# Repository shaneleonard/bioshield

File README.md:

# bioshield
Arduino shield for biomedical instrumentation. Includes an ECG, ICG, and PPG. For educational purposes.

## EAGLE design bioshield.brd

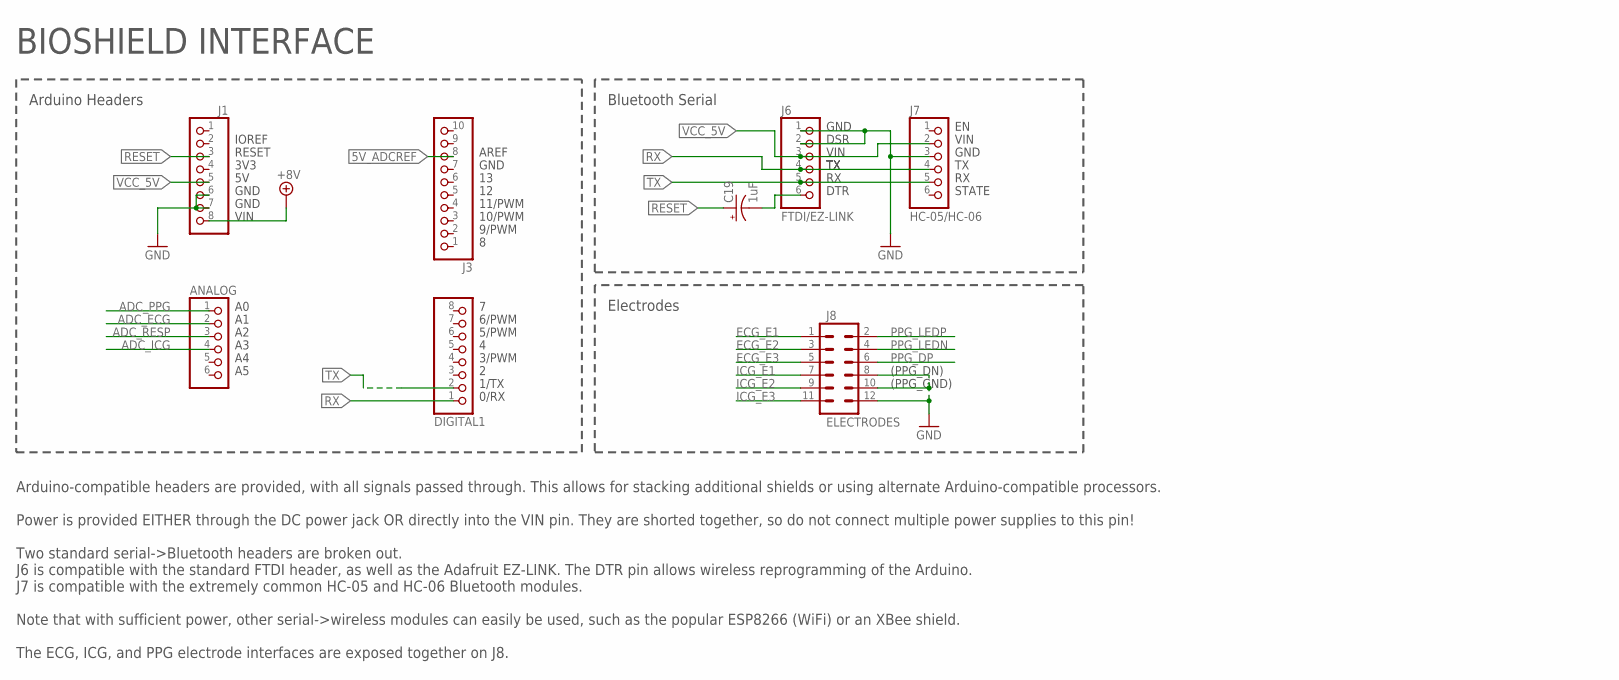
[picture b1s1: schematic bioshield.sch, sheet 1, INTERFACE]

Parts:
ANALOG: PINHD-1X6; 1X06
C19: 1uF; E2-5
DIGITAL1: PINHD-1X8TH; 1X08-TH
J1: PINHD-1X8TH; 1X08-TH
J3: PINHD-1X10TH; 1X10-TH
J6: FTDI/EZ-LINK; 1X06
J7: HC-05/HC-06; 1X06
J8: ELECTRODES; 2X6

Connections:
5V_ADCREF: J3.8; also elsewhere on the board
+8V: J1.8; also elsewhere on the board
ADC_ECG: ANALOG.2; also elsewhere on the board
ADC_ICG: ANALOG.4; also elsewhere on the board
ADC_PPG: ANALOG.1; also elsewhere on the board
ADC_RESP: ANALOG.3; also elsewhere on the board
ECG_E1: J8.1; also elsewhere on the board
ECG_E2: J8.3; also elsewhere on the board
ECG_E3: J8.5; also elsewhere on the board
GND: J1.6, J1.7, J6.1, J6.2, J7.3, J8.8, J8.10, J8.12; also elsewhere on the board
ICG_E1: J8.7; also elsewhere on the board
ICG_E2: J8.9; also elsewhere on the board
ICG_E3: J8.11; also elsewhere on the board
unnamed: C19.-, J6.6
PPG_DP: J8.6; also elsewhere on the board
PPG_LEDN: J8.4; also elsewhere on the board
PPG_LEDP: J8.2; also elsewhere on the board
RESET: C19.+, J1.3
RX: DIGITAL1.1, J6.4, J7.4
TX: DIGITAL1.2, J6.5, J7.5
VCC_5V: J1.5, J6.3, J7.2; also elsewhere on the board

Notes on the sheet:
BIOSHIELD INTERFACE
IOREF
RESET
3V3
GND
VIN
AREF
11/PWM
10/PWM
9/PWM
6/PWM
5/PWM
3/PWM
1/TX
0/RX
DSR
DTR
STATE
Arduino Headers
Bluetooth Serial
Electrodes
Arduino-compatible headers are provided, with all signals passed through. This allows for stacking additional shields or using alternate Arduino-compatible processors. Power is provided EITHER through the DC power jack OR directly into the VIN pin. They are shorted together, so do not connect multi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
(PPG_DN)
(PPG_GND)

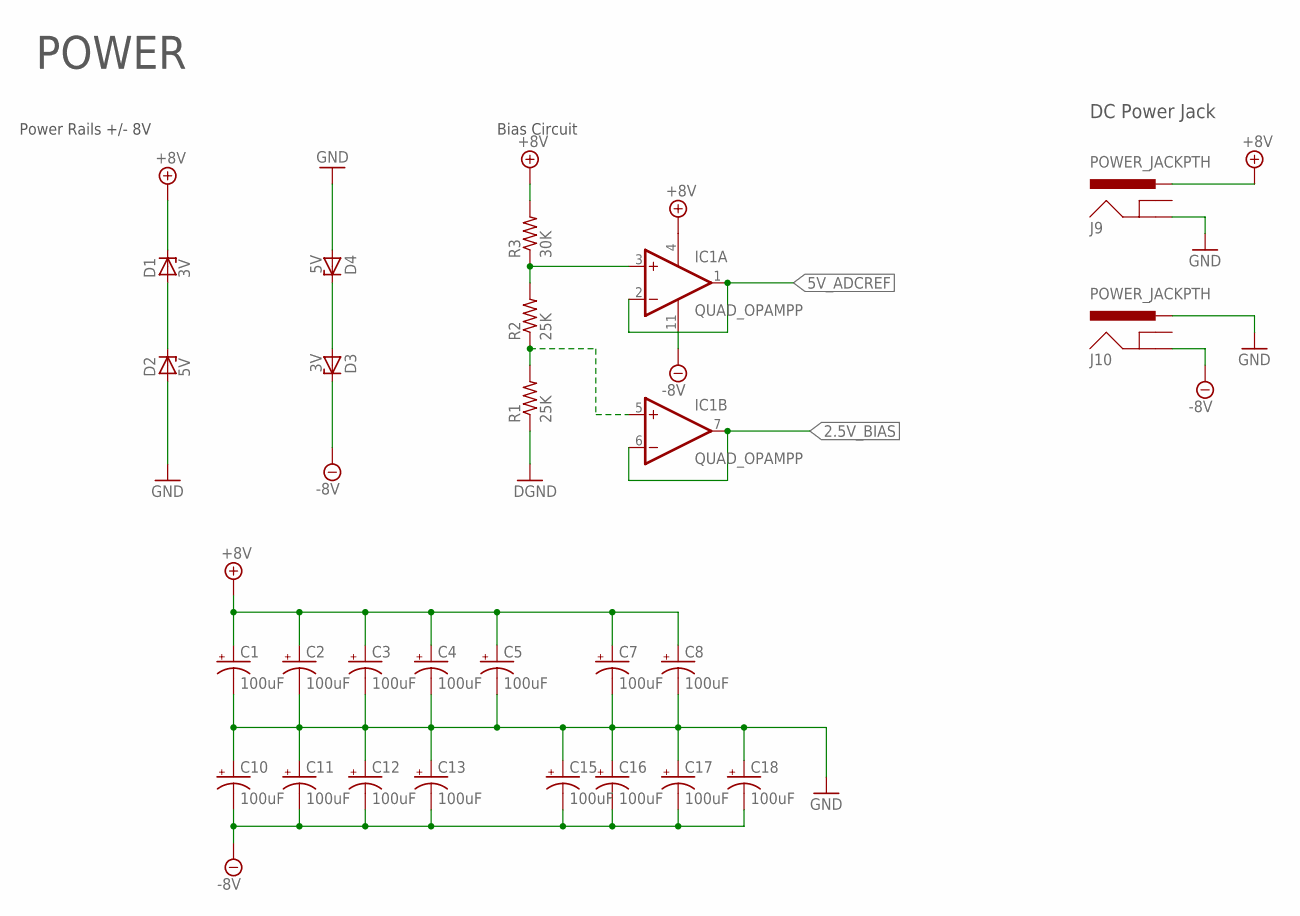
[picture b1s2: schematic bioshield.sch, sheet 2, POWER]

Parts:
C1, C2, C3, C4, C5, C7, C8, C10, C11, C12, C13, C15, C16, C17, C18: 100uF; CPOL-RADIAL-100UF-25V
D1, D3: 3V; ZDIO-10
D2, D4: 5V; ZDIO-10
IC1: QUAD_OPAMPP; DIL14
J9, J10: POWER_JACKPTH; POWER_JACK_PTH
R1, R2: 25K; 0207/10
R3: 30K; 0207/10

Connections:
2.5V_BIAS: IC1.6 (-IN), IC1.7 (OUT); also elsewhere on the board
5V_ADCREF: IC1.1 (OUT), IC1.2 (-IN); also elsewhere on the board
+8V: C1.1 (+), C2.1 (+), C3.1 (+), C4.1 (+), C5.1 (+), C7.1 (+), C8.1 (+), D1.C, IC1.4 (V+), J9.PWR, R3.2; also elsewhere on the board
-8V: C10.2 (-), C11.2 (-), C12.2 (-), C13.2 (-), C15.2 (-), C16.2 (-), C17.2 (-), C18.2 (-), D3.C, IC1.11 (V-), J10.GND; also elsewhere on the board
GND: C1.2 (-), C2.2 (-), C3.2 (-), C4.2 (-), C5.2 (-), C7.2 (-), C8.2 (-), C10.1 (+), C11.1 (+), C12.1 (+), C13.1 (+), C15.1 (+), C16.1 (+), C17.1 (+), C18.1 (+), D2.A, D4.A, J9.GND, J10.PWR, R1.1; also elsewhere on the board
unnamed: IC1.5 (+IN), R1.2, R2.1
unnamed: D1.A, D2.C
unnamed: IC1.3 (+IN), R2.2, R3.1
unnamed: D3.A, D4.C

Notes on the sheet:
POWER
Power Rails +/- 8V
Bias Circuit
DC Power Jack

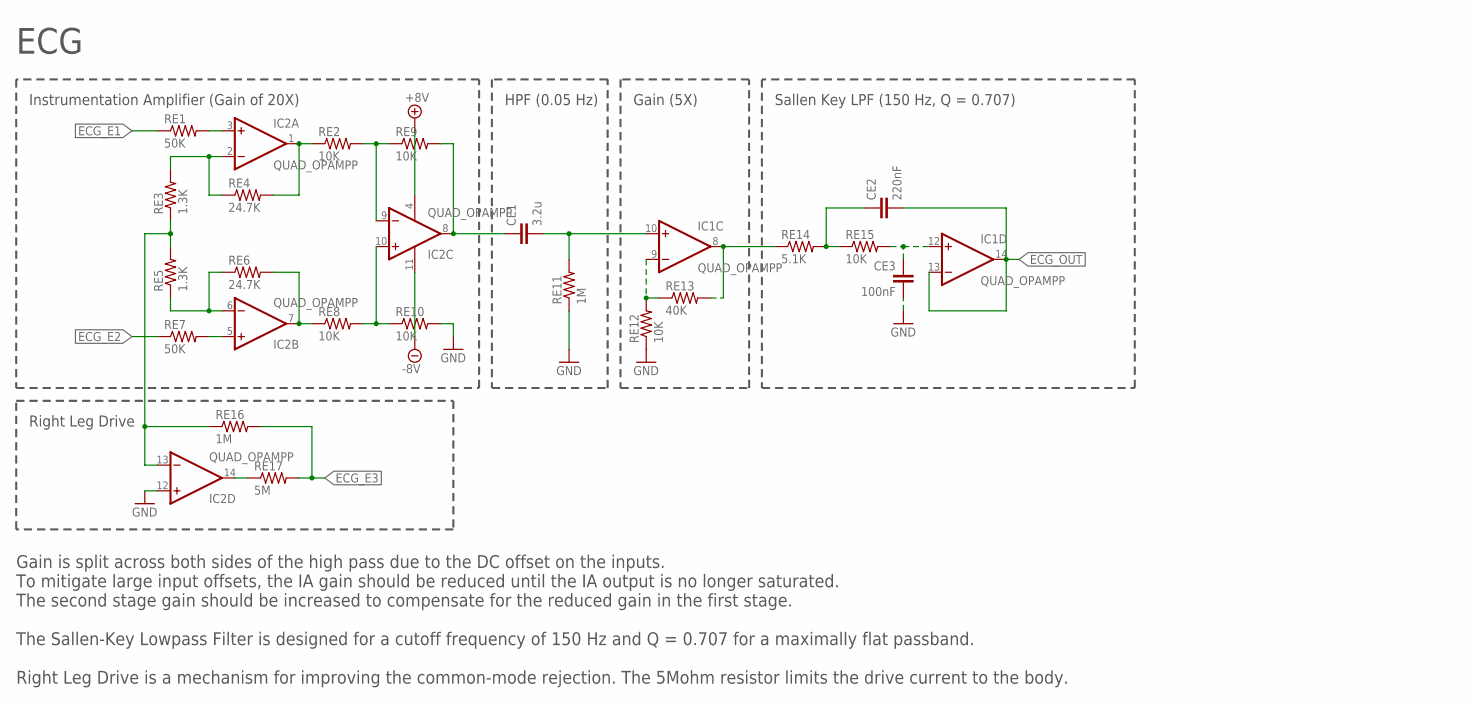
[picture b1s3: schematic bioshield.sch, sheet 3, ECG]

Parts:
CE1: 3.2u; CAP-PTH-5MM
CE2: 220nF; CAP-PTH-5MM
CE3: 100nF; CAP-PTH-5MM
IC1, IC2: QUAD_OPAMPP; DIL14
RE1, RE7: 50K; 0207/10
RE2, RE8, RE9, RE10, RE12, RE15: 10K; 0207/10
RE3, RE5: 1.3K; 0207/10
RE4, RE6: 24.7K; 0207/10
RE11, RE16: 1M; 0207/10
RE13: 40K; 0207/10
RE14: 5.1K; 0207/10
RE17: 5M; 0207/10

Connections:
+8V: IC2.4 (V+); also elsewhere on the board
-8V: IC2.11 (V-); also elsewhere on the board
ECG_E1: RE1.1; also elsewhere on the board
ECG_E2: RE7.1; also elsewhere on the board
ECG_E3: RE16.2, RE17.2; also elsewhere on the board
ECG_OUT: CE2.2, IC1.13 (-IN), IC1.14 (OUT); also elsewhere on the board
GND: CE3.2, IC2.12 (+IN), RE10.2, RE11.1, RE12.1; also elsewhere on the board
unnamed: IC1.9 (-IN), RE12.2, RE13.1
unnamed: CE1.2, IC1.10 (+IN), RE11.2
unnamed: CE3.1, IC1.12 (+IN), RE15.2
unnamed: IC1.8 (OUT), RE13.2, RE14.1
unnamed: CE2.1, RE14.2, RE15.1
unnamed: IC2.14 (OUT), RE17.1
unnamed: IC2.5 (+IN), RE7.2
unnamed: IC2.13 (-IN), RE3.1, RE5.2, RE16.1
unnamed: IC2.6 (-IN), RE5.1, RE6.1
unnamed: IC2.7 (OUT), RE6.2, RE8.1
unnamed: IC2.10 (+IN), RE8.2, RE10.1
unnamed: IC2.2 (-IN), RE3.2, RE4.1
unnamed: IC2.1 (OUT), RE2.1, RE4.2
unnamed: IC2.3 (+IN), RE1.2
unnamed: IC2.9 (-IN), RE2.2, RE9.1
unnamed: CE1.1, IC2.8 (OUT), RE9.2

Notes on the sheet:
Instrumentation Amplifier (Gain of 20X)
HPF (0.05 Hz)
Gain (5X)
Sallen Key LPF (150 Hz, Q = 0.707)
Right Leg Drive
ECG
Gain is split across both sides of the high pass due to the DC offset on the inputs. To mitigate large input offsets, the IA gain should be reduced until the IA output is no longer saturated. The second stage gain should be increased to compensate for the reduced gain in the first stage. The Sallen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

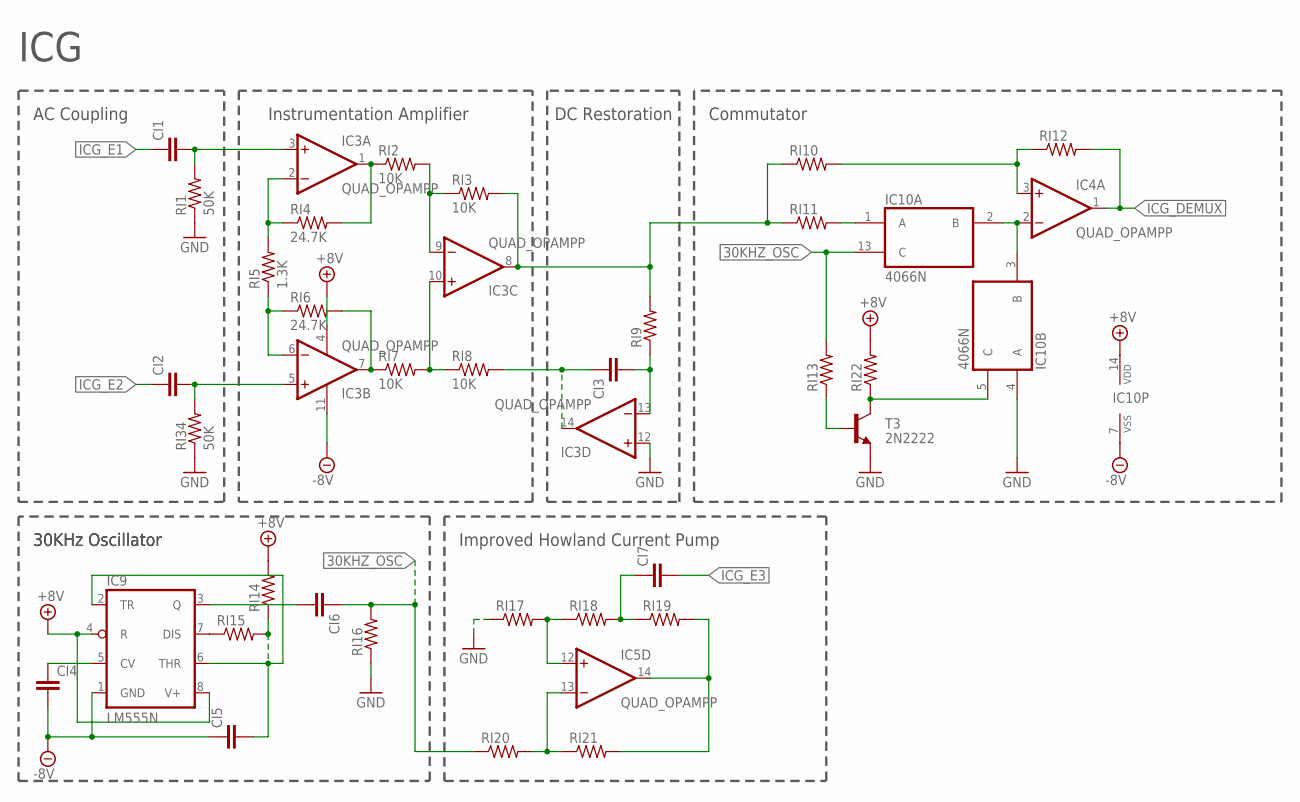
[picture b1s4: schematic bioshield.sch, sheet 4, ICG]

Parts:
CI1, CI2, CI3, CI4, CI5, CI6, CI7: CAPPTH1; CAP-PTH-5MM
IC3, IC4, IC5: QUAD_OPAMPP; DIL14
IC9: LM555N; DIL08
IC10: 4066N; DIL14
RI1, RI34: 50K; 0207/10
RI2, RI3, RI7, RI8: 10K; 0207/10
RI4, RI6: 24.7K; 0207/10
RI5: 1.3K; 0207/10
RI9, RI10, RI11, RI12, RI13, RI14, RI15, RI16, RI17, RI18, RI19, RI20, RI21, RI22: R-US_0207/10; 0207/10
T3: 2N2222; TO92-EBC-OVAL

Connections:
30KHZ_OSC: CI6.1, IC10.13 (C), RI13.2, RI16.2, RI20.1
+8V: IC3.4 (V+), IC9.4 (R), IC9.8 (V+), IC10.14 (VDD), RI14.2, RI22.2; also elsewhere on the board
-8V: CI4.2, CI5.1, IC3.11 (V-), IC9.1 (GND), IC10.7 (VSS); also elsewhere on the board
ELECTRODE3: CI7.1, RI18.2, RI19.1
GND: IC3.12 (+IN), IC10.4 (A), RI1.1, RI16.1, RI17.1, RI34.1, T3.E; also elsewhere on the board
ICG_DEMUX: IC4.1 (OUT), RI12.2; also elsewhere on the board
ICG_E1: CI1.1; also elsewhere on the board
ICG_E2: CI2.1; also elsewhere on the board
ICG_E3: CI7.2; also elsewhere on the board
unnamed: CI2.2, IC3.5 (+IN), RI34.2
unnamed: CI3.1, IC3.14 (OUT), RI8.2
unnamed: IC3.6 (-IN), RI5.1, RI6.1
unnamed: IC3.7 (OUT), RI6.2, RI7.1
unnamed: CI5.2, IC9.2 (TR), IC9.6 (THR), RI14.1, RI15.2
unnamed: IC10.1 (A), RI11.2
unnamed: IC9.7 (DIS), RI15.1
unnamed: IC4.2 (-IN), IC10.2 (B), IC10.3 (B)
unnamed: RI13.1, T3.B
unnamed: CI4.1, IC9.5 (CV)
unnamed: CI6.2, IC9.3 (Q)
unnamed: IC3.10 (+IN), RI7.2, RI8.1
unnamed: IC3.2 (-IN), RI4.1, RI5.2
unnamed: IC3.1 (OUT), RI2.1, RI4.2
unnamed: CI1.2, IC3.3 (+IN), RI1.2
unnamed: IC3.9 (-IN), RI2.2, RI3.1
unnamed: IC3.8 (OUT), RI3.2, RI9.2, RI10.1, RI11.1
unnamed: IC5.13 (-IN), RI20.2, RI21.1
unnamed: IC5.12 (+IN), RI17.2, RI18.1
unnamed: CI3.2, IC3.13 (-IN), RI9.1
unnamed: IC4.3 (+IN), RI10.2, RI12.1
RI13: IC10.5 (C), RI22.1, T3.C
V+: IC5.14 (OUT), RI19.2, RI21.2

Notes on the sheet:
ICG
AC Coupling
Instrumentation Amplifier
Commutator
30KHz Oscillator
Improved Howland Current Pump
DC Restoration

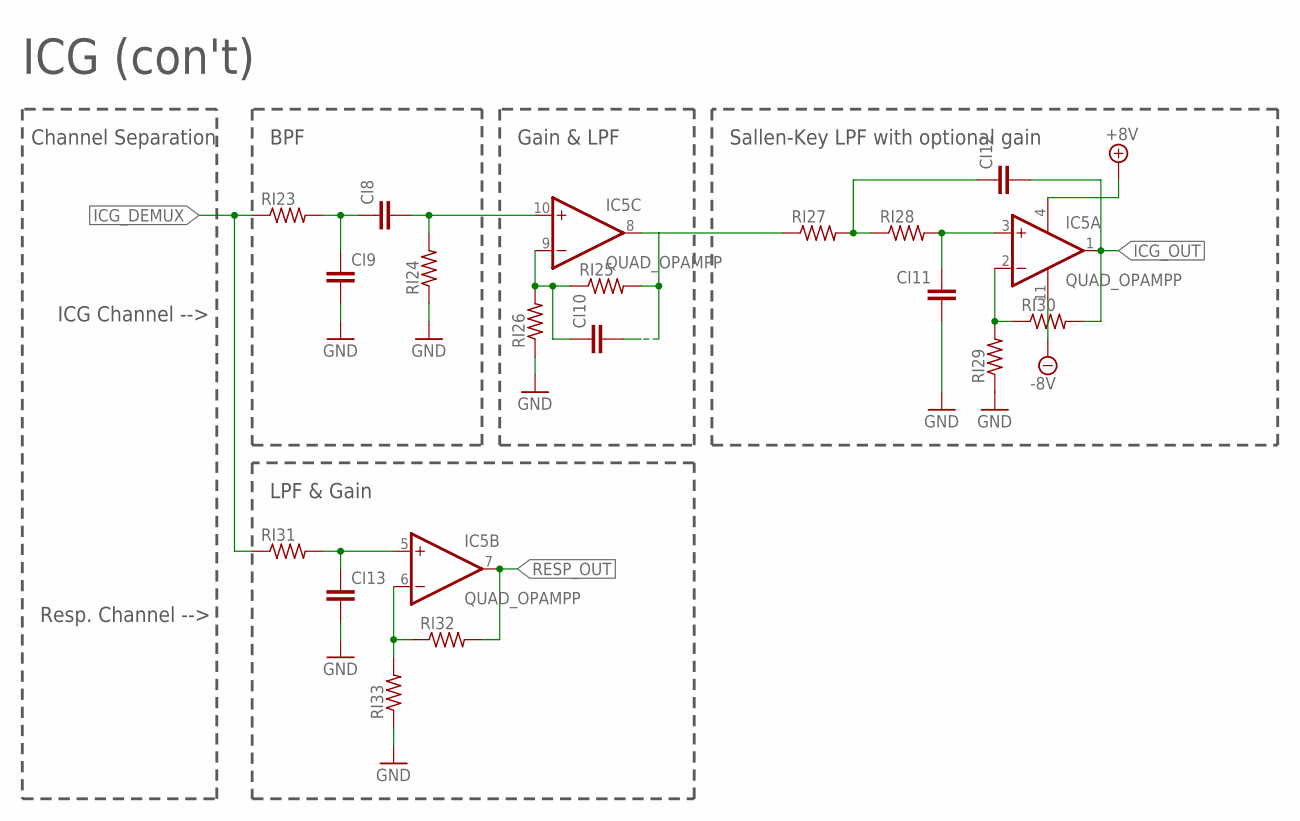
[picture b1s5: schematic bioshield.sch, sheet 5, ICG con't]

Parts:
CI8, CI9, CI10, CI11, CI12, CI13: CAPPTH1; CAP-PTH-5MM
IC5: QUAD_OPAMPP; DIL14
RI23, RI24, RI25, RI26, RI27, RI28, RI29, RI30, RI31, RI32, RI33: R-US_0207/10; 0207/10

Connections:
+8V: IC5.4 (V+); also elsewhere on the board
-8V: IC5.11 (V-); also elsewhere on the board
GND: CI9.2, CI11.2, CI13.2, RI24.1, RI26.1, RI29.1, RI33.1; also elsewhere on the board
ICG_DEMUX: RI23.1, RI31.1; also elsewhere on the board
ICG_OUT: CI12.2, IC5.1 (OUT), RI30.2; also elsewhere on the board
unnamed: CI13.1, IC5.5 (+IN), RI31.2
unnamed: CI8.2, IC5.10 (+IN), RI24.2
unnamed: CI10.1, IC5.9 (-IN), RI25.1, RI26.2
unnamed: IC5.6 (-IN), RI32.1, RI33.2
unnamed: CI12.1, RI27.2, RI28.1
unnamed: CI10.2, IC5.8 (OUT), RI25.2, RI27.1
unnamed: CI11.1, IC5.3 (+IN), RI28.2
unnamed: IC5.2 (-IN), RI29.2, RI30.1
unnamed: CI8.1, CI9.1, RI23.2
RESP_OUT: IC5.7 (OUT), RI32.2; also elsewhere on the board

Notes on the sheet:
ICG (con't)
BPF
Gain & LPF
Sallen-Key LPF with optional gain
LPF & Gain
Channel Separation
ICG Channel -->
Resp. Channel -->

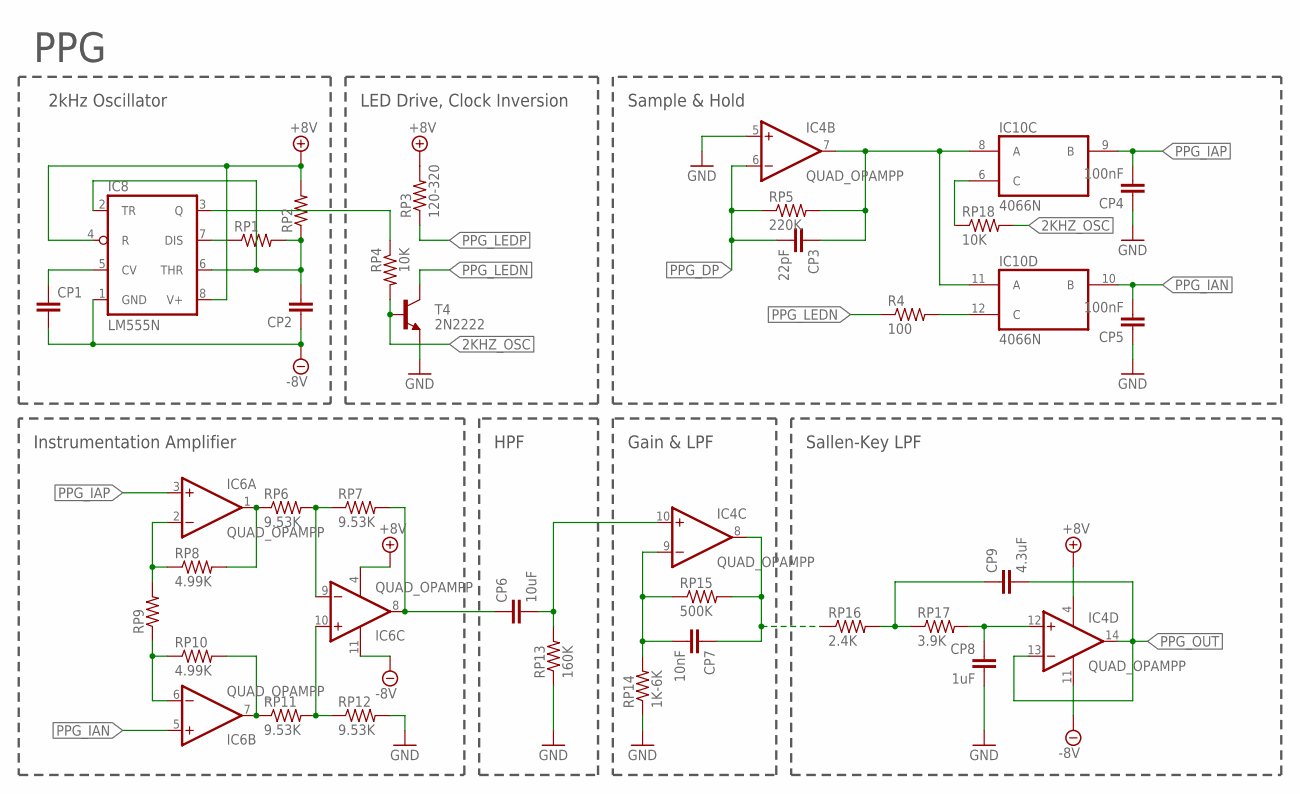
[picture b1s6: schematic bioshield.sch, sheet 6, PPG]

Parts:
CP1, CP2: CAPPTH1; CAP-PTH-5MM
CP3: 22pF; CAP-PTH-5MM
CP4, CP5: 100nF; CAP-PTH-5MM
CP6: 10uF; CAP-PTH-5MM
CP7: 10nF; CAP-PTH-5MM
CP8: 1uF; CAP-PTH-5MM
CP9: 4.3uF; CAP-PTH-5MM
IC4, IC6: QUAD_OPAMPP; DIL14
IC8: LM555N; DIL08
IC10: 4066N; DIL14
R4: 100; 0207/10
RP1, RP2, RP9: R-US_0207/10; 0207/10
RP3: 120-320; 0207/10
RP4, RP18: 10K; 0207/10
RP5: 220K; 0207/10
RP6, RP7, RP11, RP12: 9.53K; 0207/10
RP8, RP10: 4.99K; 0207/10
RP13: 160K; 0207/10
RP14: 1K-6K; 0207/10
RP15: 500K; 0207/10
RP16: 2.4K; 0207/10
RP17: 3.9K; 0207/10
T4: 2N2222; TO92-EBC-OVAL

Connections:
2KHZ_OSC: RP4.2, RP18.2, T4.B
+8V: IC4.4 (V+), IC6.4 (V+), IC8.4 (R), IC8.8 (V+), RP2.2, RP3.2; also elsewhere on the board
-8V: CP1.2, CP2.1, IC4.11 (V-), IC6.11 (V-), IC8.1 (GND); also elsewhere on the board
GND: CP4.1, CP5.1, CP8.2, IC4.5 (+IN), RP12.2, RP13.1, RP14.1, T4.E; also elsewhere on the board
unnamed: IC6.6 (-IN), RP9.1, RP10.1
unnamed: IC6.7 (OUT), RP10.2, RP11.1
unnamed: IC6.10 (+IN), RP11.2, RP12.1
unnamed: IC8.7 (DIS), RP1.1
unnamed: CP1.1, IC8.5 (CV)
unnamed: IC6.2 (-IN), RP8.1, RP9.2
unnamed: IC10.6 (C), RP18.1
unnamed: IC6.1 (OUT), RP6.1, RP8.2
unnamed: CP2.2, IC8.2 (TR), IC8.6 (THR), RP1.2, RP2.1
unnamed: IC6.9 (-IN), RP6.2, RP7.1
unnamed: CP6.1, IC6.8 (OUT), RP7.2
unnamed: CP3.1, IC4.7 (OUT), IC10.8 (A), IC10.11 (A), RP5.2
unnamed: CP6.2, IC4.10 (+IN), RP13.2
unnamed: IC10.12 (C), R4.2
unnamed: CP7.2, IC4.9 (-IN), RP14.2, RP15.1
unnamed: CP7.1, IC4.8 (OUT), RP15.2, RP16.1
unnamed: CP9.1, RP16.2, RP17.1
unnamed: CP8.1, IC4.12 (+IN), RP17.2
unnamed: IC8.3 (Q), RP4.1
PPG_DP: CP3.2, IC4.6 (-IN), RP5.1; also elsewhere on the board
PPG_IAN: CP5.2, IC6.5 (+IN), IC10.10 (B)
PPG_IAP: CP4.2, IC6.3 (+IN), IC10.9 (B)
PPG_LEDN: R4.1, T4.C; also elsewhere on the board
PPG_LEDP: RP3.1; also elsewhere on the board
PPG_OUT: CP9.2, IC4.13 (-IN), IC4.14 (OUT); also elsewhere on the board

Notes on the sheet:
PPG
2kHz Oscillator
LED Drive, Clock Inversion
Sample & Hold
Instrumentation Amplifier
HPF
Gain & LPF
Sallen-Key LPF

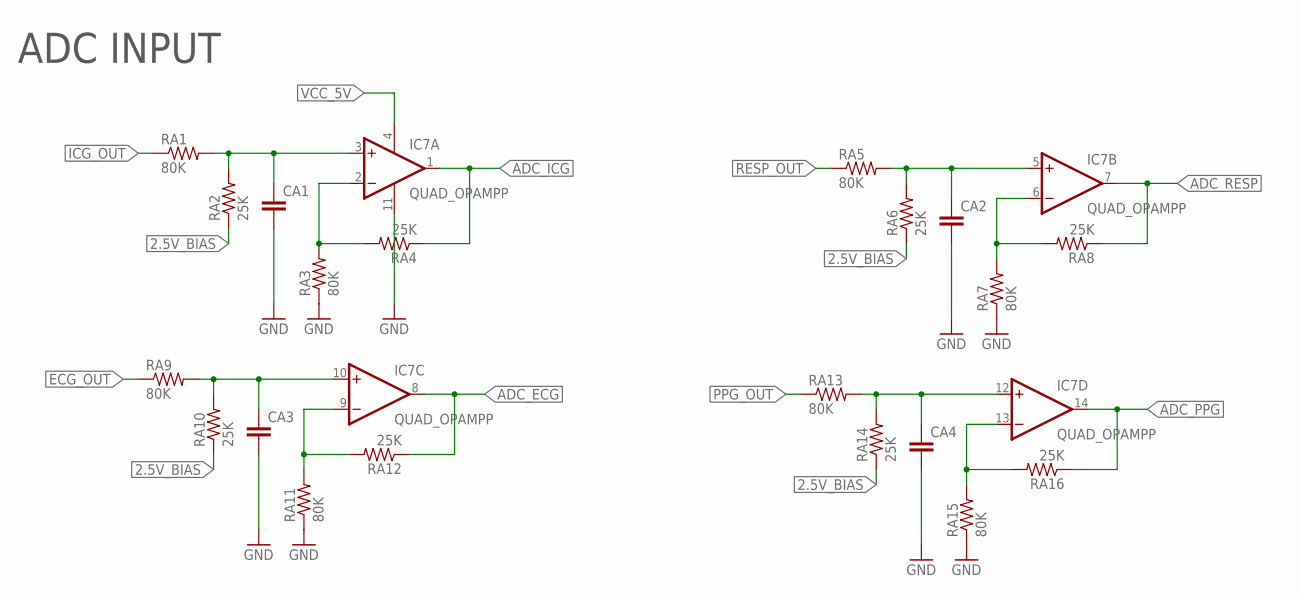
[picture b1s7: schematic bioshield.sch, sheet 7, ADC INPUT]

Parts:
CA1, CA2, CA3, CA4: CAPPTH1; CAP-PTH-5MM
IC7: QUAD_OPAMPP; DIL14
RA1, RA3, RA5, RA7, RA9, RA11, RA13, RA15: 80K; 0207/10
RA2, RA4, RA6, RA8, RA10, RA12, RA14, RA16: 25K; 0207/10

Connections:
2.5V_BIAS: RA2.1, RA6.1, RA10.1, RA14.1; also elsewhere on the board
ADC_ECG: IC7.8 (OUT), RA12.1; also elsewhere on the board
ADC_ICG: IC7.1 (OUT), RA4.1; also elsewhere on the board
ADC_PPG: IC7.14 (OUT), RA16.1; also elsewhere on the board
ADC_RESP: IC7.7 (OUT), RA8.1; also elsewhere on the board
ECG_OUT: RA9.1; also elsewhere on the board
GND: CA1.2, CA2.2, CA3.2, CA4.2, IC7.11 (V-), RA3.1, RA7.1, RA11.1, RA15.1; also elsewhere on the board
ICG_OUT: RA1.1; also elsewhere on the board
unnamed: CA1.1, IC7.3 (+IN), RA1.2, RA2.2
unnamed: IC7.2 (-IN), RA3.2, RA4.2
unnamed: CA2.1, IC7.5 (+IN), RA5.2, RA6.2
unnamed: IC7.6 (-IN), RA7.2, RA8.2
unnamed: CA3.1, IC7.10 (+IN), RA9.2, RA10.2
unnamed: IC7.9 (-IN), RA11.2, RA12.2
unnamed: CA4.1, IC7.12 (+IN), RA13.2, RA14.2
unnamed: IC7.13 (-IN), RA15.2, RA16.2
PPG_OUT: RA13.1; also elsewhere on the board
RESP_OUT: RA5.1; also elsewhere on the board
VCC_5V: IC7.4 (V+); also elsewhere on the board

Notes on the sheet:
ADC INPUT

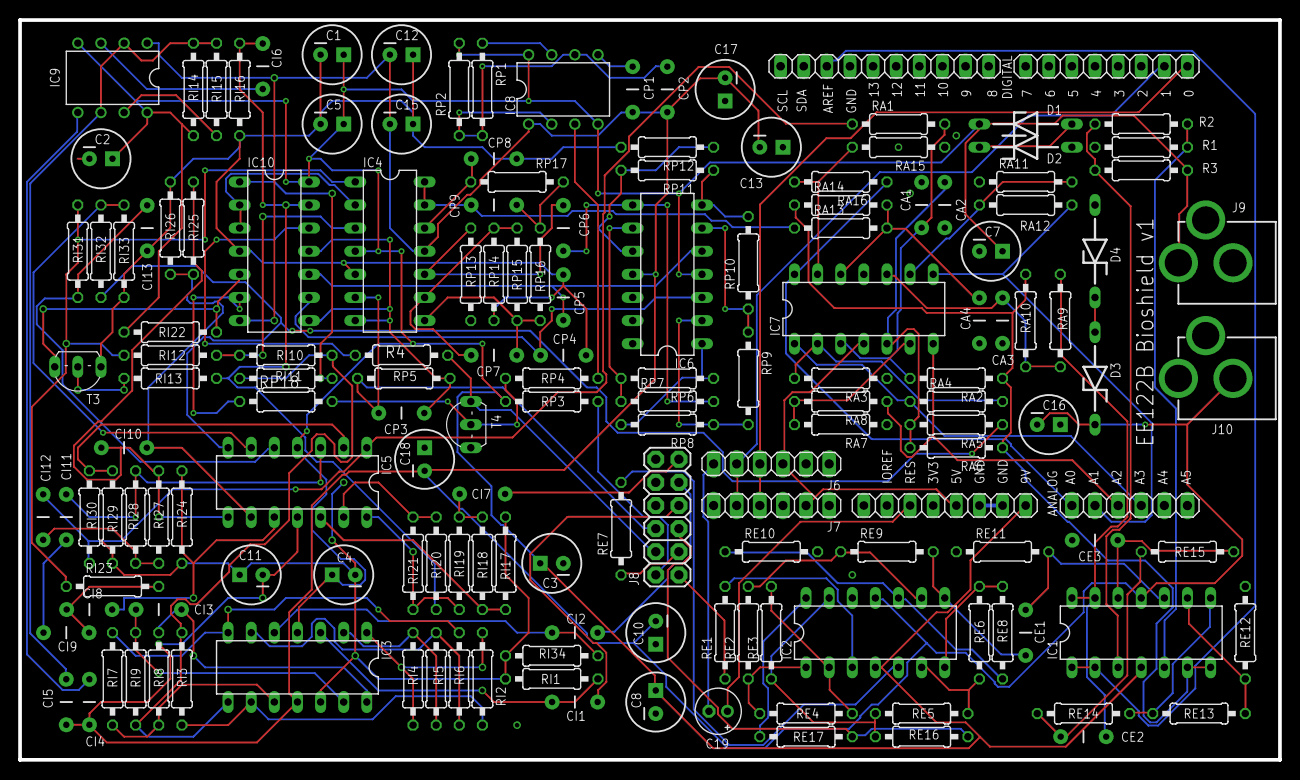
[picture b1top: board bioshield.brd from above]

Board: 2 copper layers, 138.4 x 81.3 mm, 159 parts (1 on the bottom side), 112 nets.

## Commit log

2016-05-22 All blocks are in progress
2016-05-23 Schematic nearly complete
2016-05-24 Redesign
2016-05-25 Grouped items in layout
2016-05-25 ICG somewhat good
2016-05-26 Revision 1
2016-05-26 Schematic visually consistent
2016-05-28 Pre-assembly

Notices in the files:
parts and their libraries:
SparkFun-Passives: Licensing: Creative Commons ShareAlike 4.0 International - https://creativecommons.org/licenses/by-sa/4.0
